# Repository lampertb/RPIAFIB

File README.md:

# RPIAFIB
AFIB Detection using Raspberry Pi Compute Module

This is a project created by Yifan Ge and Ben Lampert for the CS241 Embedded Workshop class(http://web.stanford.edu/class/cs241/). The intention is to create an open source AFIB detection wearable which can be used to diagnose patients with the condition.

Please reference the instructable for more information on assembling the board.
http://www.instructables.com/id/rPI-Atrial-Fibrillation-Detection-Board/

To install run

sudo sh ./install.sh

Run software:
cd Software
sudo ./execute_afib_detect

Todo:
Software:
-Improve ECG Capture code
-Improve integration between the algorithm detection and sampling code
Hardware:
-Lipo charger circuit does not allow for the board to be powered while charging the LED, need to find a solution for this. Integrated charger?

USE AT YOUR OWN RISK: This project involves ECG measurements which can be dangerous if not done correctly. It is your responsibility to evaluate your own medical and physical condition, or that of your clients, and to independently determine whether to perform, use or adapt any of the information or content on this repository. By voluntarily undertaking the project displayed on this website, you assume the risk of any resulting injury.

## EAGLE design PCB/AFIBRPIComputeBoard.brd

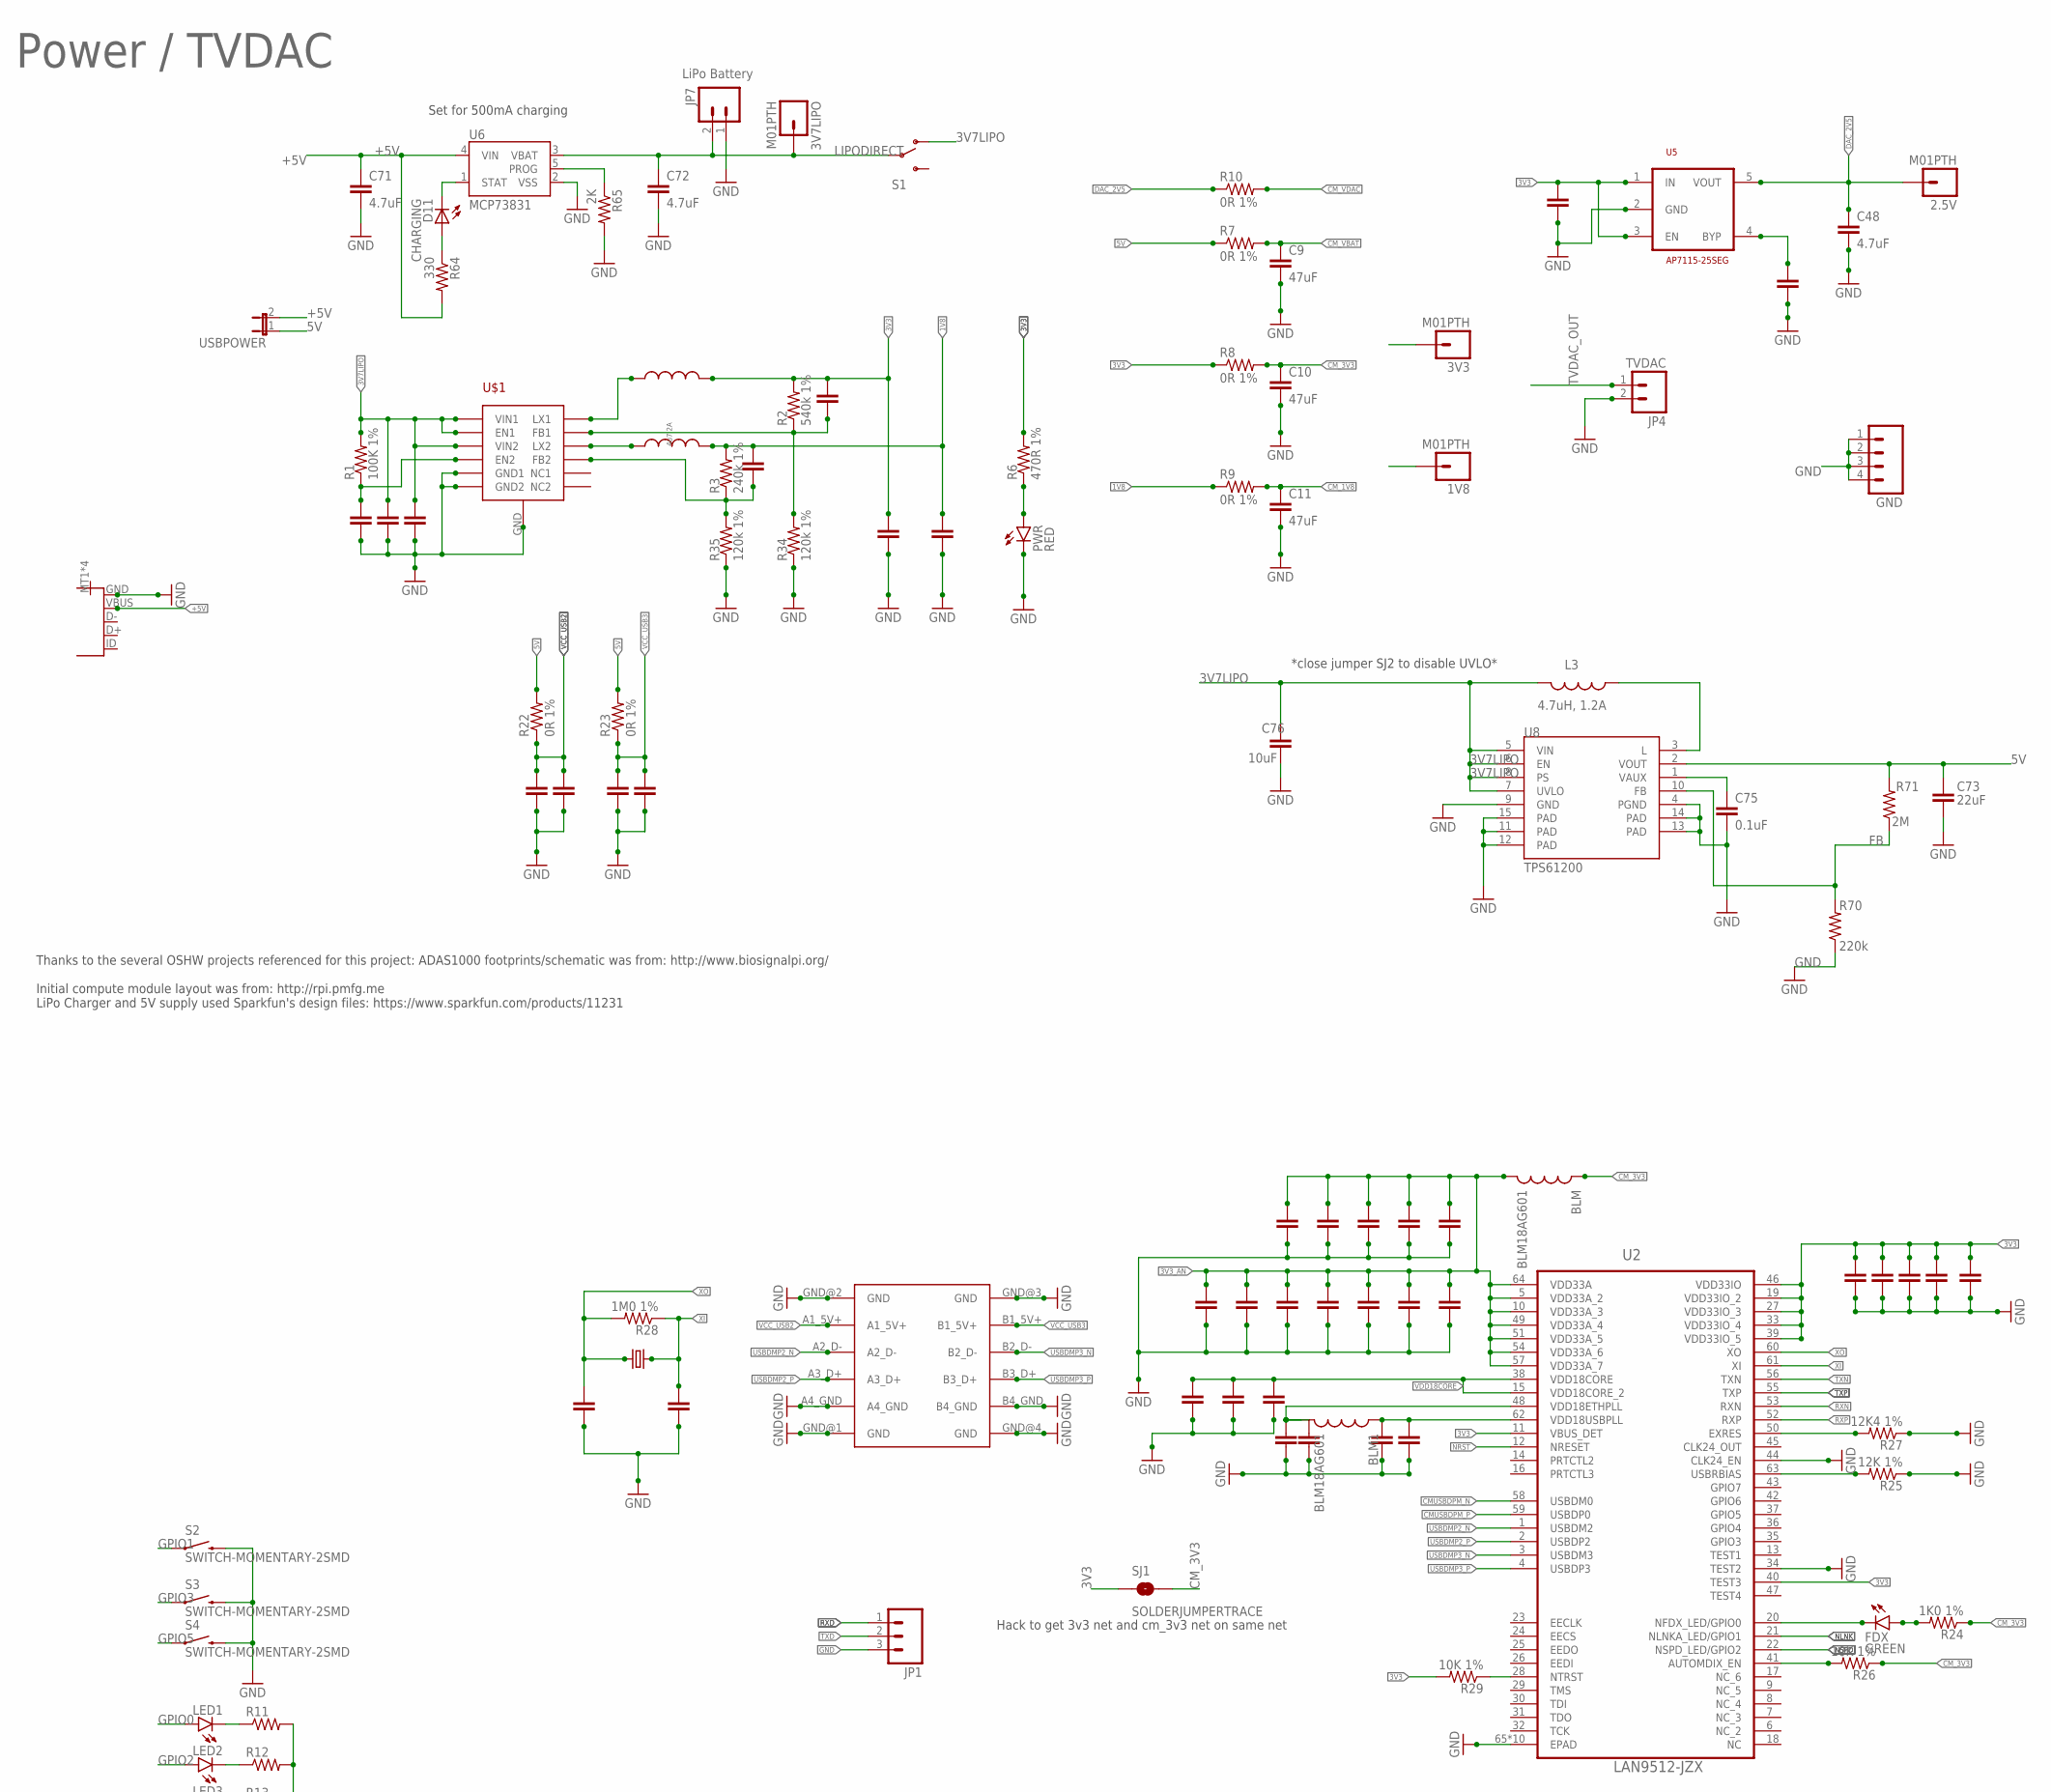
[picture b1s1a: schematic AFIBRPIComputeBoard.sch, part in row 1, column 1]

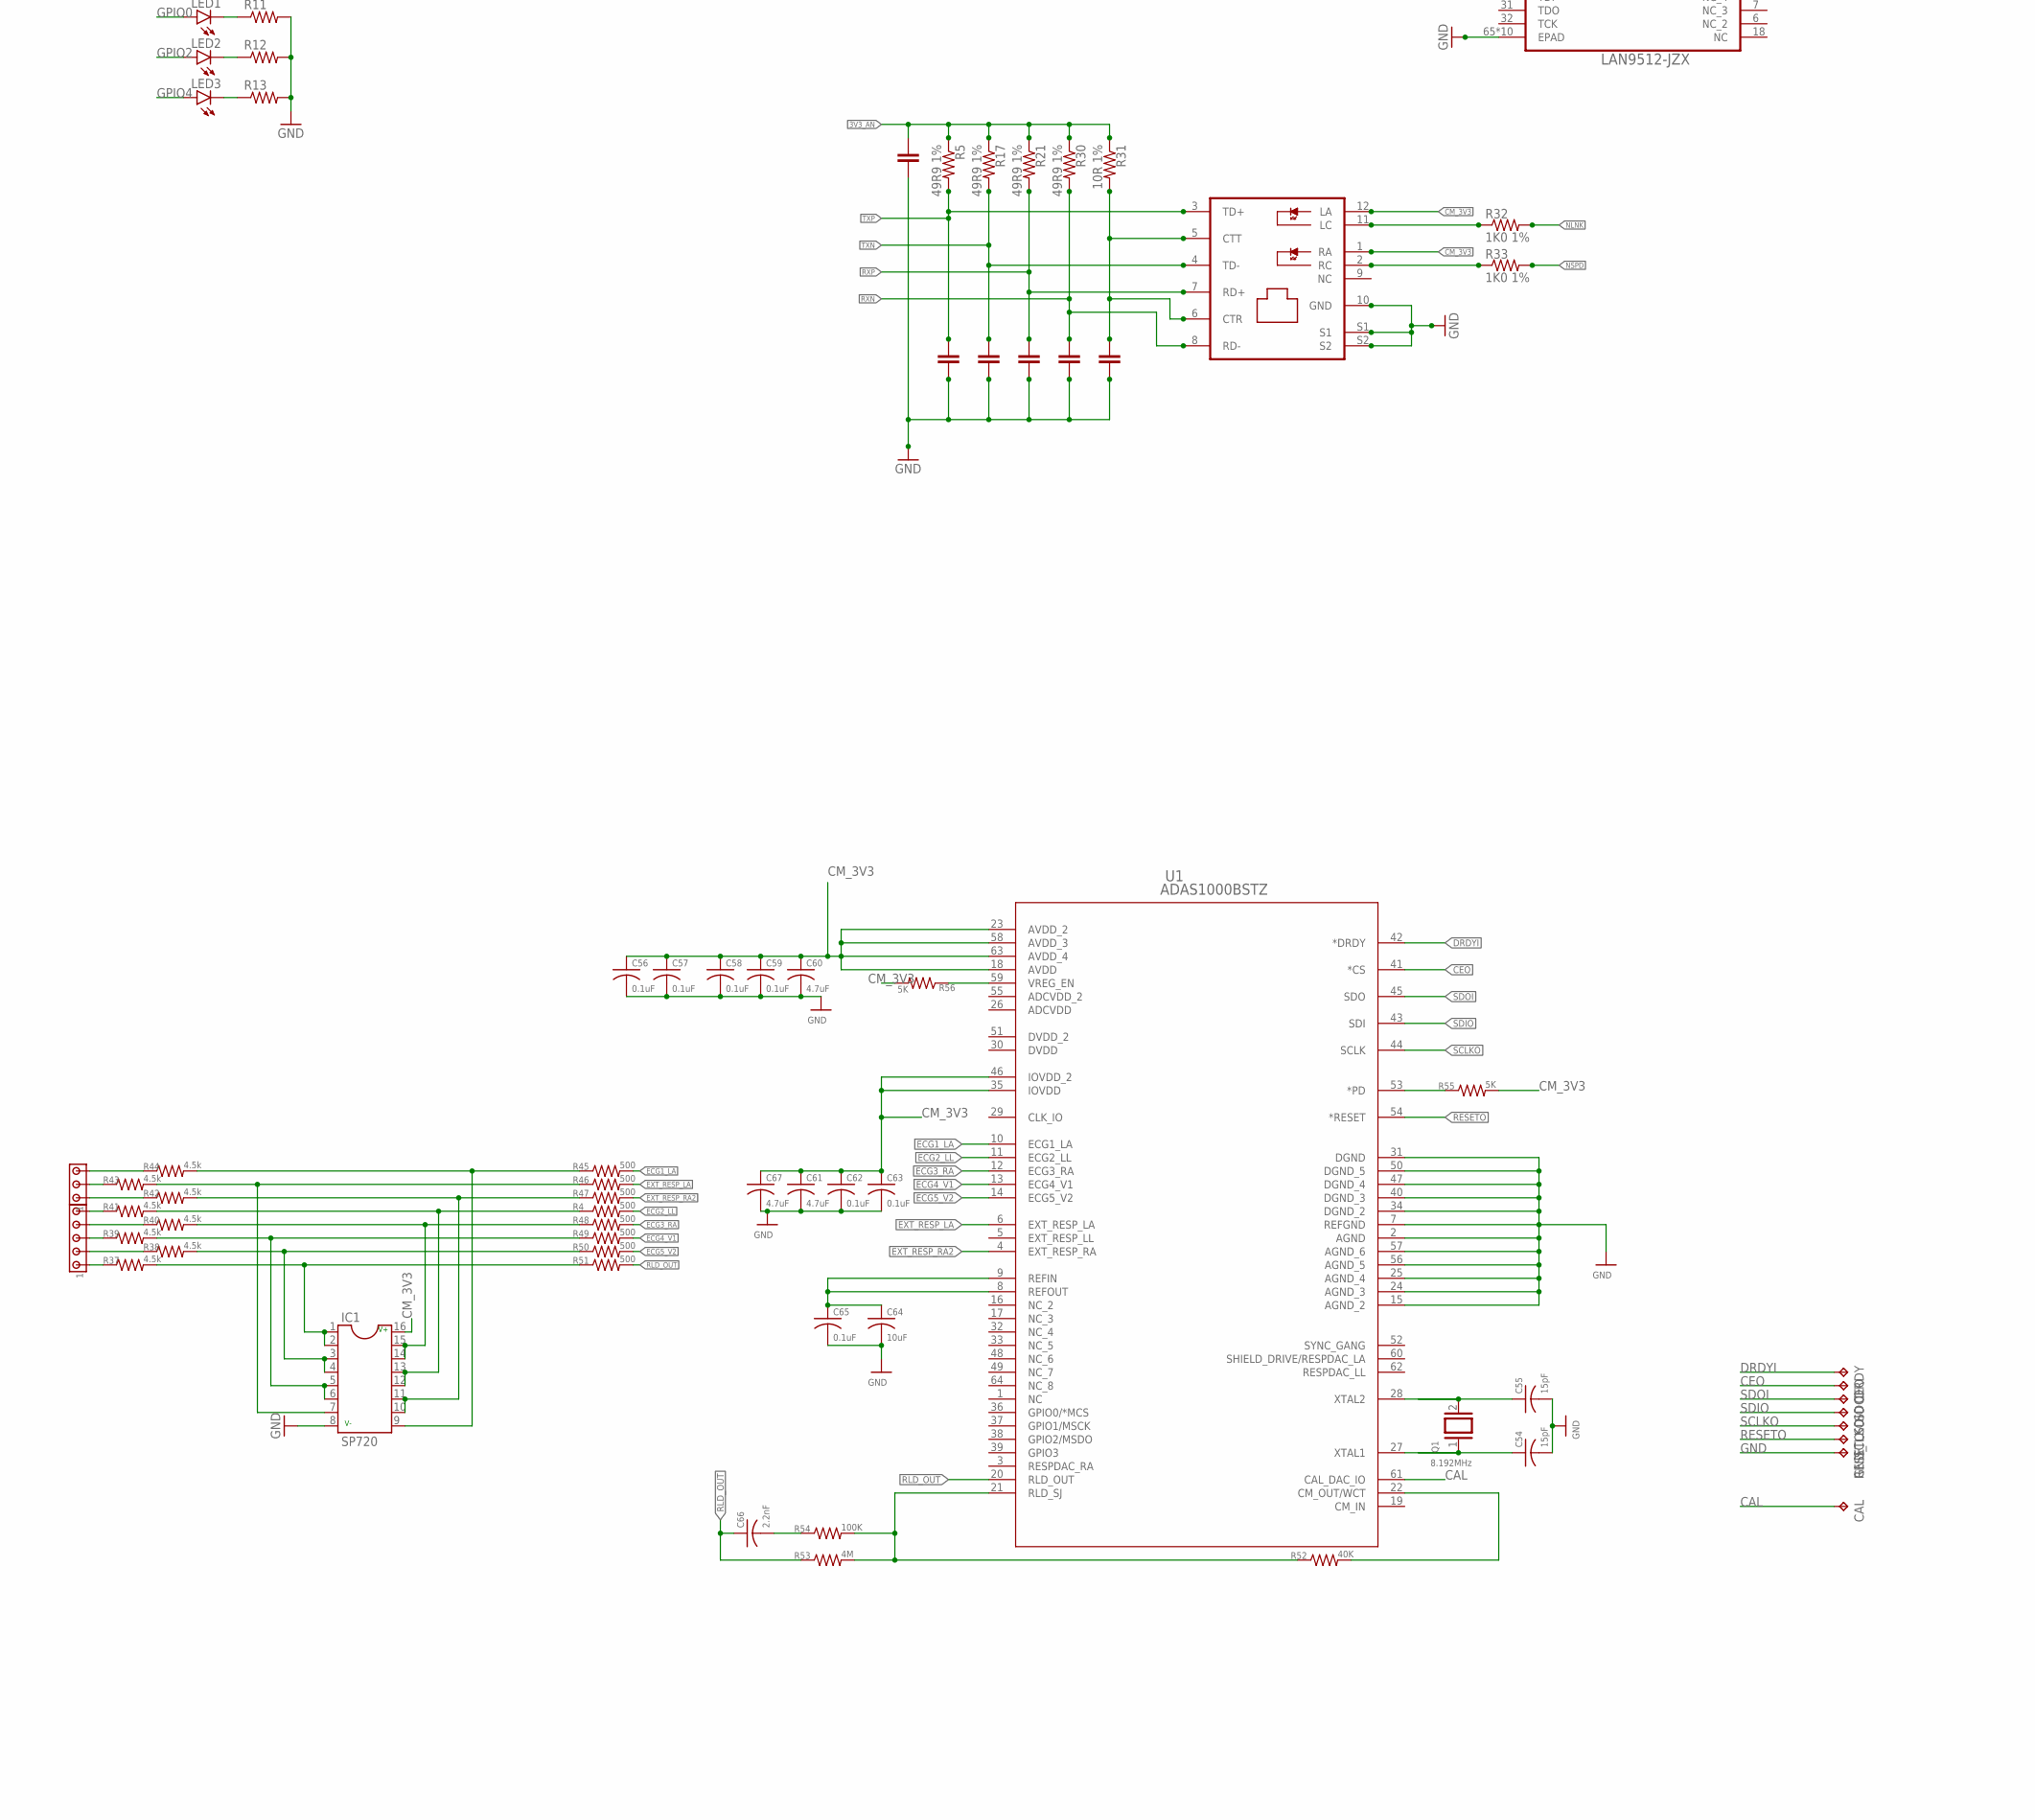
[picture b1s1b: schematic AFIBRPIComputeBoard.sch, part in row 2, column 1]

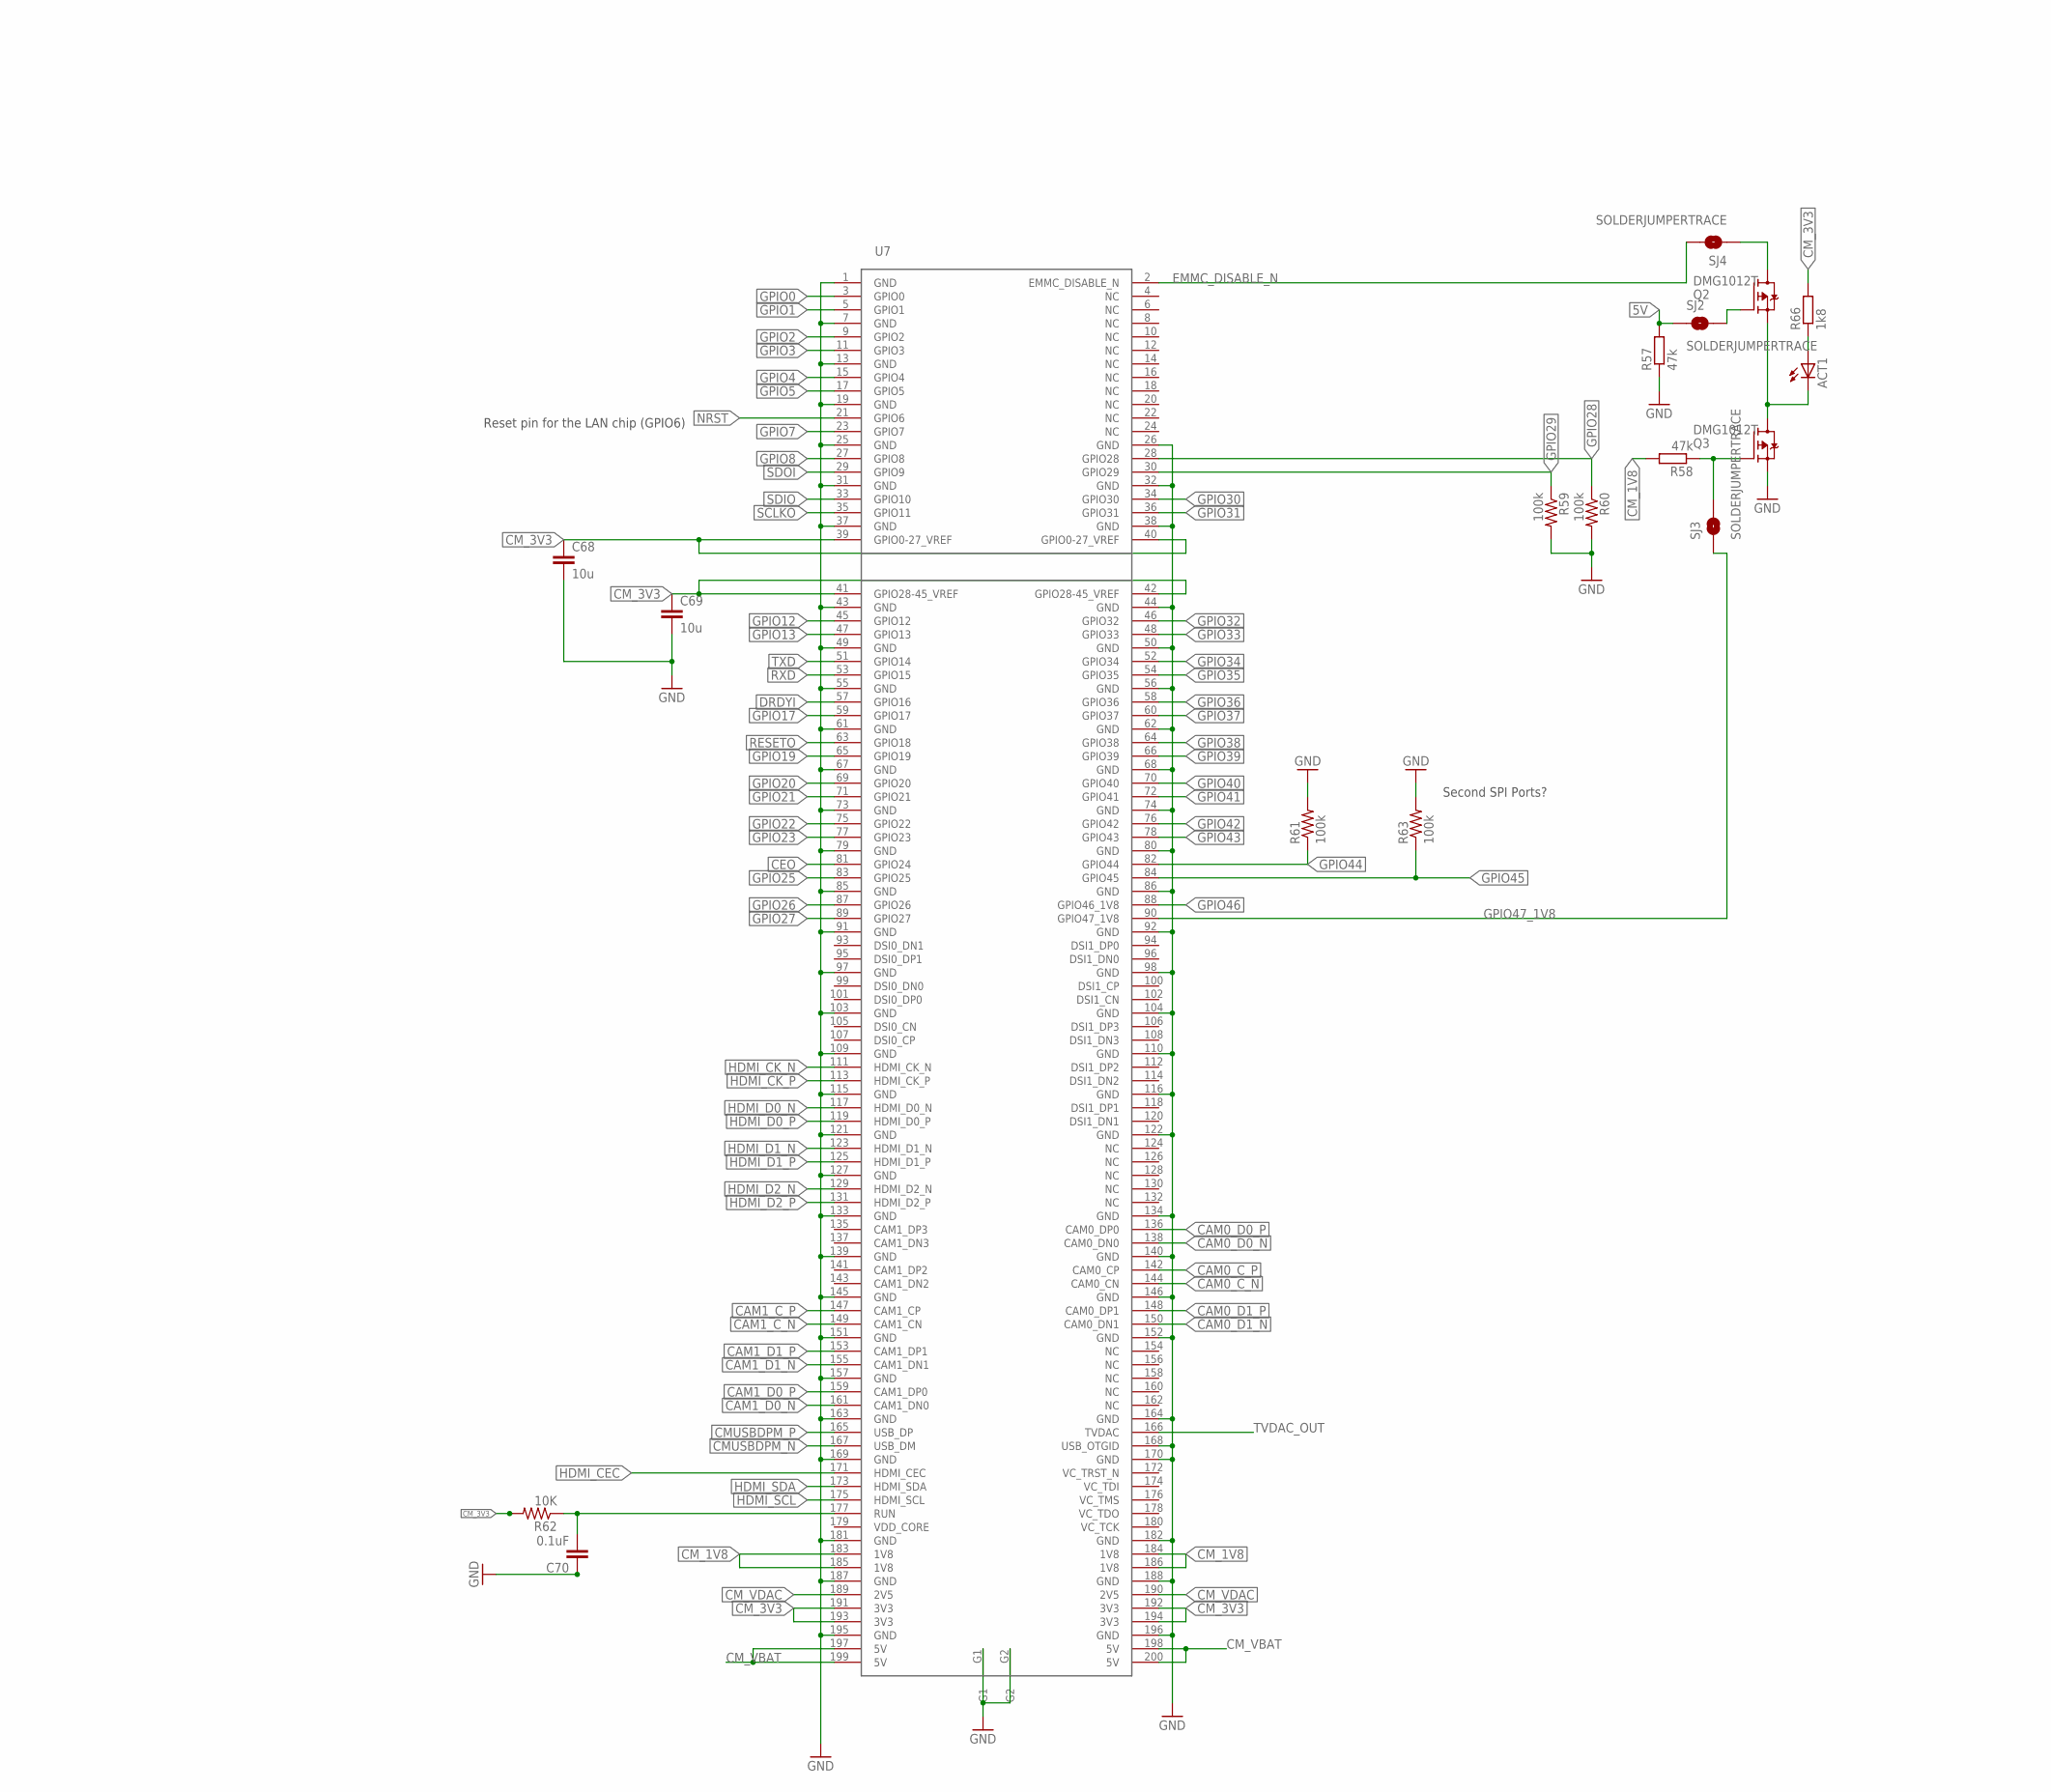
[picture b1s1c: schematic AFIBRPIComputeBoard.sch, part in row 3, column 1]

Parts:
1V8, 2.5V, 3V3, 3V7LIPO: M01PTH; 1X01
ACT1: LEDCHIP-LED0603; CHIP-LED0603
BLM, BLM1: BLM18AG601; 0603
C2, C17, C18, C19, C20, C22, C23, C24, C25, C26, C27, C28, C29, C30, C31, C32, C33, C34, C35, C39, C40, C41, C42, C46, C47: 100nF; 0402
C3, C4, C6, C8: 10uF; 0805
C5, C7, C16, C43: 15pf 50V 5%; 0402
C9, C10, C11: 47uF; 0603-CAP
C14, C15: 100uF 10v; 1206
C21, C36: 4u7; 0402
C37, C38: 12pf; 0402
C44: 47uf 10v; 0805
C45: 1uF; 0402
C48: 4.7uF; 0603-CAP
C49: 22nF; 0805
C50: 47uF 10V; 0805
C51, C52: 100pF; 0402
C54, C55: 15pF; C0805
C56, C57, C58, C59, C62, C63, C65: 0.1uF; C0805
C60, C61, C67: 4.7uF; C0805
C64: 10uF; C0805
C66: 2.2nF; C0805
C68, C69: 10u; 0603-CAP
C70, C75: 0.1uF; 0603-CAP
C71, C72: 4.7uF; 0402-CAP
C73: 22uF; 0603-CAP
C76: 10uF; 0603-CAP
CAL: TPPAD1-13; P1-13
CEO: TPPAD1-13; P1-13
D11: CHARGING; LED-0603
DRDY: TPPAD1-13; P1-13
FDX: GREEN; LED-0603
GND: M04PTH; 1X04
GND_: TPPAD1-13; P1-13
IC1: SP720; DIL16
J1: J3011; J30
J2: JUMPERS; 10X03MTA
J3: JUMPERS; 10X05MTA
JP1: M03PTH; 1X03
JP3: USB-IDMICRO; USB-MICRO
JP4: TVDAC; 1X02
JP7: LiPo Battery; JST-2-SMD
L1, L2: 4.7u 2A; SRN4018
L3: 4.7uH, 1.2A; CDRH2D09
LED1, LED2, LED3: LED0603; LED-0603
PWR: RED; LED-0603
Q1: 8.192MHz; QS
Q2, Q3: DMG1012T; SC75_INFINEON
R1: 100K 1%; 0402-RES
R2: 540k 1%; 0402-RES
R3: 240k 1%; 0402-RES
R4, R45, R46, R47, R48, R49, R50, R51: 500; 0603-RES
R5, R17, R21, R30: 49R9 1%; 0402-RES
R6: 470R 1%; 0402-RES
R7, R8, R9, R10, R22, R23: 0R 1%; 0603-RES
R11, R12, R13: RESISTOR0603; 0603-RES
R24, R32, R33: 1K0 1%; 0402-RES
R25: 12K 1%; 0402-RES
R26, R29: 10K 1%; 0402-RES
R27: 12K4 1%; 0402-RES
R28: 1M0 1%; 0402-RES
R31: 10R 1%; 0402-RES
R34, R35: 120k 1%; 0402-RES
R37, R38, R39, R40, R41, R42, R43, R44: 4.5k; 0603-RES
R52: 40K; 0603-RES
R53: 4M; 0603-RES
R54: 100K; 0603-RES
R55, R56: 5K; 0603-RES
R57, R58: 47k; R0603
R59, R60, R61, R63: 100k; 0603-RES
R62: 10K; 0603-RES
R64: 330; 0402-RES
R65: 2K; 0402-RES
R66: 1k8; R0603
R70: 220k; 0402-RES
R71: 2M; 0402-RES
RESETO: TPPAD1-13; P1-13
S1: SWITCH-SPDT-SMD-A; SWITCH-SPST-SMD-A
S2, S3, S4: SWITCH-MOMENTARY-2SMD; TACTILE-SWITCH-SMD
SCLKO: TPPAD1-13; P1-13
SDIO: TPPAD1-13; P1-13
SDOI: TPPAD1-13; P1-13
SJ1, SJ2, SJ3, SJ4: SOLDERJUMPERTRACE; SJ_2S-TRACE
U1: ADAS1000BSTZ; ST_64_2
U2: LAN9512-JZX; QFN50P900X900X100-65N
U5: AP7115-25SEG; SOT353
U6: MCP73831; SOT23-5
U7: RASPI; SO-DIMM
U8: TPS61200; QFN-10_PAD
U$1: WDFN-12L
USB1: 72309USB-TYPE-A; 72309
USBPOWER: JUMPER-2PTH; 1X02
Y1: CRYSTAL5X3; CRYSTAL-SMD-5X3

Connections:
1V8: C8.1, C52.1, L2.P$2 (2), R3.2, R9.1
3V3: C6.1, C21.1, C32.1, C33.1, C34.1, C35.1, C45.1, C51.1, L1.P$2 (2), R2.2, R6.2, R8.1, R29.2, SJ1.1, U2.11 (VBUS_DET), U2.19 (VDD33IO_2), U2.27 (VDD33IO_3), U2.33 (VDD33IO_4), U2.39 (VDD33IO_5), U2.40 (TEST3), U2.46 (VDD33IO), U5.1 (IN), U5.3 (EN)
3V3_AN: BLM.2, C17.1, C18.1, C19.1, C20.1, C22.1, C23.1, C24.1, C25.1, C26.1, C27.1, C28.1, C29.1, C46.1, R5.1, R17.1, R21.1, R30.1, R31.1, U2.5 (VDD33A_2), U2.10 (VDD33A_3), U2.49 (VDD33A_4), U2.51 (VDD33A_5), U2.54 (VDD33A_6), U2.57 (VDD33A_7), U2.64 (VDD33A)
3V7LIPO: C3.1, C4.1, C76.1, L3.P$2 (2), R1.2, S1.1 (O), U8.5 (VIN), U8.6 (EN), U8.7 (UVLO), U8.8 (PS), U$1.1 (VIN2), U$1.6 (EN1), U$1.7 (VIN1)
5V: C73.1, R7.1, R22.2, R23.2, R57.2, R71.2, SJ2.1, U8.2 (VOUT), USBPOWER.1
+5V: C71.1, JP3.VBUS, R64.2, U6.4 (VIN), USBPOWER.2
CAL: CAL.TP, U1.61 (CAL_DAC_IO)
CAM0_C_N: U7.144 (CAM0_CN)
CAM0_C_P: U7.142 (CAM0_CP)
CAM0_D0_N: U7.138 (CAM0_DN0)
CAM0_D0_P: U7.136 (CAM0_DP0)
CAM0_D1_N: U7.150 (CAM0_DN1)
CAM0_D1_P: U7.148 (CAM0_DP1)
CAM1_C_N: U7.149 (CAM1_CN)
CAM1_C_P: U7.147 (CAM1_CP)
CAM1_D0_N: U7.161 (CAM1_DN0)
CAM1_D0_P: U7.159 (CAM1_DP0)
CAM1_D1_N: U7.155 (CAM1_DN1)
CAM1_D1_P: U7.153 (CAM1_DP1)
CEO: CEO.TP, U1.41 (*CS), U7.81 (GPIO24)
CMUSBDPM_N: U2.58 (USBDM0), U7.167 (USB_DM)
CMUSBDPM_P: U2.59 (USBDP0), U7.165 (USB_DP)
CM_1V8: 1V8.1, C11.1, R9.2, R58.2, U7.183 (1V8), U7.184 (1V8), U7.185 (1V8), U7.186 (1V8)
CM_3V3: 3V3.1, BLM.1, C10.1, C56.1, C57.1, C58.1, C59.1, C60.1, C61.1, C62.1, C63.1, C67.1, C68.1, C69.1, IC1.16, J1.1 (RA), J1.12 (LA), R8.2, R24.1, R26.1, R55.2, R56.2, R62.2, R66.2, SJ1.2, U1.18 (AVDD), U1.23 (AVDD_2), U1.35 (IOVDD), U1.46 (IOVDD_2), U1.58 (AVDD_3), U1.63 (AVDD_4), U7.39 (GPIO0-27_VREF), U7.40 (GPIO0-27_VREF), U7.41 (GPIO28-45_VREF), U7.42 (GPIO28-45_VREF), U7.191 (3V3), U7.192 (3V3), U7.193 (3V3), U7.194 (3V3)
CM_VBAT: C9.1, R7.2, U7.197 (5V), U7.198 (5V), U7.199 (5V), U7.200 (5V)
CM_VDAC: R10.2, U7.189 (2V5), U7.190 (2V5)
DAC_2V5: 2.5V.1, C48.1, R10.1, U5.5 (VOUT)
DRDYI: DRDY.TP, U1.42 (*DRDY), U7.57 (GPIO16)
ECG1_LA: R45.2, U1.10 (ECG1_LA)
ECG2_LL: R4.2, U1.11 (ECG2_LL)
ECG3_RA: R48.2, U1.12 (ECG3_RA)
ECG4_V1: R49.2, U1.13 (ECG4_V1)
ECG5_V2: R50.2, U1.14 (ECG5_V2)
EMMC_DISABLE_N: SJ4.2, U7.2 (EMMC_DISABLE_N)
EXT_RESP_LA: R46.2, U1.6 (EXT_RESP_LA)
EXT_RESP_RA2: R47.2, U1.4 (EXT_RESP_RA)
FB: R70.2, R71.1, U8.10 (FB)
GND: C2.2, C3.2, C4.2, C5.2, C6.2, C7.2, C8.2, C9.2, C10.2, C11.2, C14.2, C15.2, C16.2, C17.2, C18.2, C19.2, C20.2, C21.2, C22.2, C23.2, C24.2, C25.2, C26.2, C27.2, C28.2, C29.2, C30.2, C31.2, C32.2, C33.2, C34.2, C35.2, C36.2, C37.2, C38.2, C39.2, C40.2, C41.2, C42.2, C43.2, C44.2, C45.2, C46.2, C47.2, C48.2, C49.2, C50.2, C54.2, C55.2, C56.2, C57.2, C58.2, C59.2, C60.2, C61.2, C62.2, C63.2, C64.2, C65.2, C67.2, C68.2, C69.2, C70.1, C71.2, C72.2, C73.2, C75.2, C76.2, GND.1, GND.2, GND.3, GND.4, GND_.TP, IC1.8, J1.10 (GND), J1.S1, J1.S2, JP1.3, JP3.GND, JP4.2, JP7.1, Q3.3 (S), R11.2, R12.2, R13.2, R25.1, R27.1, R34.1, R35.1, R57.1, R59.2, R60.2, R61.2, R63.2, R65.2, R70.1, S2.3 (2), S3.3 (2), S4.3 (2), U1.2 (AGND), U1.7 (REFGND), U1.15 (AGND_2), U1.24 (AGND_3), U1.25 (AGND_4), U1.31 (DGND), U1.34 (DGND_2), U1.40 (DGND_3), U1.47 (DGND_4), U1.50 (DGND_5), U1.56 (AGND_5), U1.57 (AGND_6), U2.34 (TEST2), U2.44 (CLK24_EN), U2.65 (EPAD), U2.GND@1 (EPAD), U2.GND@2 (EPAD), U2.GND@3 (EPAD), U2.GND@4 (EPAD), U2.GND@5 (EPAD), U2.GND@6 (EPAD), U2.GND@7 (EPAD), U2.GND@8 (EPAD), U2.GND@9 (EPAD), U5.2 (GND), U6.2 (VSS), U7.1 (GND), U7.7 (GND), U7.13 (GND), U7.19 (GND), U7.25 (GND), U7.26 (GND), U7.31 (GND), U7.32 (GND), U7.37 (GND), U7.38 (GND), U7.43 (GND), U7.44 (GND), U7.49 (GND), U7.50 (GND), U7.55 (GND), U7.56 (GND), U7.61 (GND), U7.62 (GND), U7.67 (GND), U7.68 (GND), U7.73 (GND), U7.74 (GND), U7.79 (GND), U7.80 (GND), U7.85 (GND), U7.86 (GND), U7.91 (GND), U7.92 (GND), U7.97 (GND), U7.98 (GND), U7.103 (GND), U7.104 (GND), U7.109 (GND), U7.110 (GND), U7.115 (GND), U7.116 (GND), U7.121 (GND), U7.122 (GND), U7.127 (GND), U7.133 (GND), U7.134 (GND), U7.139 (GND), U7.140 (GND), U7.145 (GND), U7.146 (GND), U7.151 (GND), U7.152 (GND), U7.157 (GND), U7.163 (GND), U7.164 (GND), U7.168 (USB_OTGID), U7.169 (GND), U7.170 (GND), U7.181 (GND), U7.182 (GND), U7.187 (GND), U7.188 (GND), U7.195 (GND), U7.196 (GND), U7.G1, U7.G2, U8.4 (PGND), U8.9 (GND), U8.11 (PAD), U8.12 (PAD), U8.13 (PAD), U8.14 (PAD), U8.15 (PAD), U$1.3 (GND1), U$1.9 (GND2), U$1.GND, USB1.A4_GND, USB1.B4_GND, USB1.GND@1 (GND), USB1.GND@2 (GND), USB1.GND@3 (GND), USB1.GND@4 (GND)
GPIO0: LED1.A, U7.3 (GPIO0)
GPIO1: S2.1, U7.5 (GPIO1)
GPIO2: LED2.A, U7.9 (GPIO2)
GPIO3: S3.1, U7.11 (GPIO3)
GPIO4: LED3.A, U7.15 (GPIO4)
GPIO5: S4.1, U7.17 (GPIO5)
GPIO7: U7.23 (GPIO7)
GPIO8: U7.27 (GPIO8)
GPIO12: U7.45 (GPIO12)
GPIO13: U7.47 (GPIO13)
GPIO17: U7.59 (GPIO17)
GPIO19: U7.65 (GPIO19)
GPIO20: U7.69 (GPIO20)
GPIO21: U7.71 (GPIO21)
GPIO22: U7.75 (GPIO22)
GPIO23: U7.77 (GPIO23)
GPIO25: U7.83 (GPIO25)
GPIO26: U7.87 (GPIO26)
GPIO27: U7.89 (GPIO27)
GPIO28: R60.1, U7.28 (GPIO28)
GPIO29: R59.1, U7.30 (GPIO29)
GPIO30: U7.34 (GPIO30)
GPIO31: U7.36 (GPIO31)
GPIO32: U7.46 (GPIO32)
GPIO33: U7.48 (GPIO33)
GPIO34: U7.52 (GPIO34)
GPIO35: U7.54 (GPIO35)
GPIO36: U7.58 (GPIO36)
GPIO37: U7.60 (GPIO37)
GPIO38: U7.64 (GPIO38)
GPIO39: U7.66 (GPIO39)
GPIO40: U7.70 (GPIO40)
GPIO41: U7.72 (GPIO41)
GPIO42: U7.76 (GPIO42)
GPIO43: U7.78 (GPIO43)
GPIO44: R61.1, U7.82 (GPIO44)
GPIO45: R63.1, U7.84 (GPIO45)
GPIO46: U7.88 (GPIO46_1V8)
GPIO47_1V8: SJ3.1, U7.90 (GPIO47_1V8)
HDMI_CEC: U7.171 (HDMI_CEC)
HDMI_CK_N: U7.111 (HDMI_CK_N)
HDMI_CK_P: U7.113 (HDMI_CK_P)
HDMI_D0_N: U7.117 (HDMI_D0_N)
HDMI_D0_P: U7.119 (HDMI_D0_P)
HDMI_D1_N: U7.123 (HDMI_D1_N)
HDMI_D1_P: U7.125 (HDMI_D1_P)
HDMI_D2_N: U7.129 (HDMI_D2_N)
HDMI_D2_P: U7.131 (HDMI_D2_P)
HDMI_SCL: U7.175 (HDMI_SCL)
HDMI_SDA: U7.173 (HDMI_SDA)
JUMPERS: J2.1, R42.1
LIPODIRECT: 3V7LIPO.1, C72.1, JP7.2, S1.2, U6.3 (VBAT)
unnamed: L1.P$1 (1), U$1.8 (LX1)
unnamed: C51.2, R2.1, R34.2, U$1.4 (FB1)
unnamed: C2.1, R1.1, U$1.12 (EN2)
unnamed: L2.P$1 (1), U$1.2 (LX2)
unnamed: C52.2, R3.1, R35.2, U$1.10 (FB2)
unnamed: PWR.A, R6.1
unnamed: Q2.2 (D), SJ4.1
unnamed: Q3.1 (G), R58.1, SJ3.2
unnamed: LED3.C, R13.1
unnamed: LED2.C, R12.1
unnamed: FDX.A, R24.2
unnamed: LED1.C, R11.1
unnamed: Q2.1 (G), SJ2.2
unnamed: R25.2, U2.63 (USBRBIAS)
unnamed: J3.1, R37.1
unnamed: C47.1, U5.4 (BYP)
unnamed: BLM1.1, C41.1, C42.1, U2.62 (VDD18USBPLL)
unnamed: BLM1.2, C39.1, C40.1, U2.48 (VDD18ETHPLL)
unnamed: R26.2, U2.41 (AUTOMDIX_EN)
unnamed: R27.2, U2.50 (EXRES)
unnamed: R29.1, U2.28 (NTRST)
unnamed: J1.11 (LC), R32.1
unnamed: J1.2 (RC), R33.1
unnamed: C49.1, J1.5 (CTT), J1.6 (CTR), R31.2
unnamed: FDX.C, U2.20 (NFDX_LED/GPIO0)
unnamed: J3.2, R38.1
unnamed: J3.3, R39.1
unnamed: J3.4, R40.1
unnamed: J3.5, R41.1
unnamed: J2.2, R43.1
unnamed: J2.3, R44.1
unnamed: IC1.9, R44.2, R45.1
unnamed: IC1.7, R43.2, R46.1
unnamed: IC1.3, IC1.4, R38.2, R50.1
unnamed: IC1.5, IC1.6, R39.2, R49.1
unnamed: IC1.1, IC1.2, R37.2, R51.1
unnamed: IC1.14, IC1.15, R40.2, R48.1
unnamed: IC1.12, IC1.13, R4.1, R41.2
unnamed: IC1.10, IC1.11, R42.2, R47.1
unnamed: C55.1, Q1.2, U1.28 (XTAL2)
unnamed: C54.1, Q1.1, U1.27 (XTAL1)
unnamed: C66.2, R54.1
unnamed: R55.1, U1.53 (*PD)
unnamed: R56.1, U1.59 (VREG_EN)
unnamed: R52.2, U1.22 (CM_OUT/WCT)
unnamed: C64.1, C65.1, U1.8 (REFOUT), U1.9 (REFIN)
unnamed: R52.1, R53.2, R54.2, U1.21 (RLD_SJ)
unnamed: ACT1.C, Q2.3 (S), Q3.2 (D)
unnamed: D11.A, R64.1
unnamed: L3.P$1 (1), U8.3 (L)
unnamed: C75.1, U8.1 (VAUX)
unnamed: ACT1.A, R66.1
NLNK: R32.2, U2.21 (NLNKA_LED/GPIO1)
NRST: U2.12 (NRESET), U7.21 (GPIO6)
NSPD: R33.2, U2.22 (NSPD_LED/GPIO2)
PROG: R65.1, U6.5 (PROG)
RESETO: RESETO.TP, U1.54 (*RESET), U7.63 (GPIO18)
RLD_OUT: C66.1, R51.2, R53.1, U1.20 (RLD_OUT)
RUNPIN: C70.2, R62.1, U7.177 (RUN)
RXD: JP1.1, U7.53 (GPIO15)
RXN: C43.1, J1.8 (RD-), R30.2, U2.53 (RXN)
RXP: C16.1, J1.7 (RD+), R21.2, U2.52 (RXP)
SCLKO: SCLKO.TP, U1.44 (SCLK), U7.35 (GPIO11)
SDIO: SDIO.TP, U1.43 (SDI), U7.33 (GPIO10)
SDOI: SDOI.TP, U1.45 (SDO), U7.29 (GPIO9)
STAT: D11.C, U6.1 (STAT)
TVDAC_OUT: JP4.1, U7.166 (TVDAC)
TXD: JP1.2, U7.51 (GPIO14)
TXN: C7.1, J1.4 (TD-), R17.2, U2.56 (TXN)
TXP: C5.1, J1.3 (TD+), R5.2, U2.55 (TXP)
USBDMP2_N: U2.1 (USBDM2), USB1.A2_D-
USBDMP2_P: U2.2 (USBDP2), USB1.A3_D+
USBDMP3_N: U2.3 (USBDM3), USB1.B2_D-
USBDMP3_P: U2.4 (USBDP3), USB1.B3_D+
VCC_USB2: C14.1, C44.1, R22.1, USB1.A1_5V+
VCC_USB3: C15.1, C50.1, R23.1, USB1.B1_5V+
VDD18CORE: C30.1, C31.1, C36.1, U2.15 (VDD18CORE_2), U2.38 (VDD18CORE)
XI: C37.1, R28.1, U2.61 (XI), Y1.3 (2)
XO: C38.1, R28.2, U2.60 (XO), Y1.1

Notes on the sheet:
Power / TVDAC
Second SPI Ports?
Reset pin for the LAN chip (GPIO6)
Set for 500mA charging
*close jumper SJ2 to disable UVLO*
Hack to get 3v3 net and cm_3v3 net on same net
Thanks to the several OSHW projects referenced for this project: ADAS1000 footprints/schematic was from: http://www.biosignalpi.org/ Initial compute module layout was from: http://rpi.pmfg.me LiPo Charger and 5V supply used Sparkfun's design files: https://www.sparkfun.com/products/11231

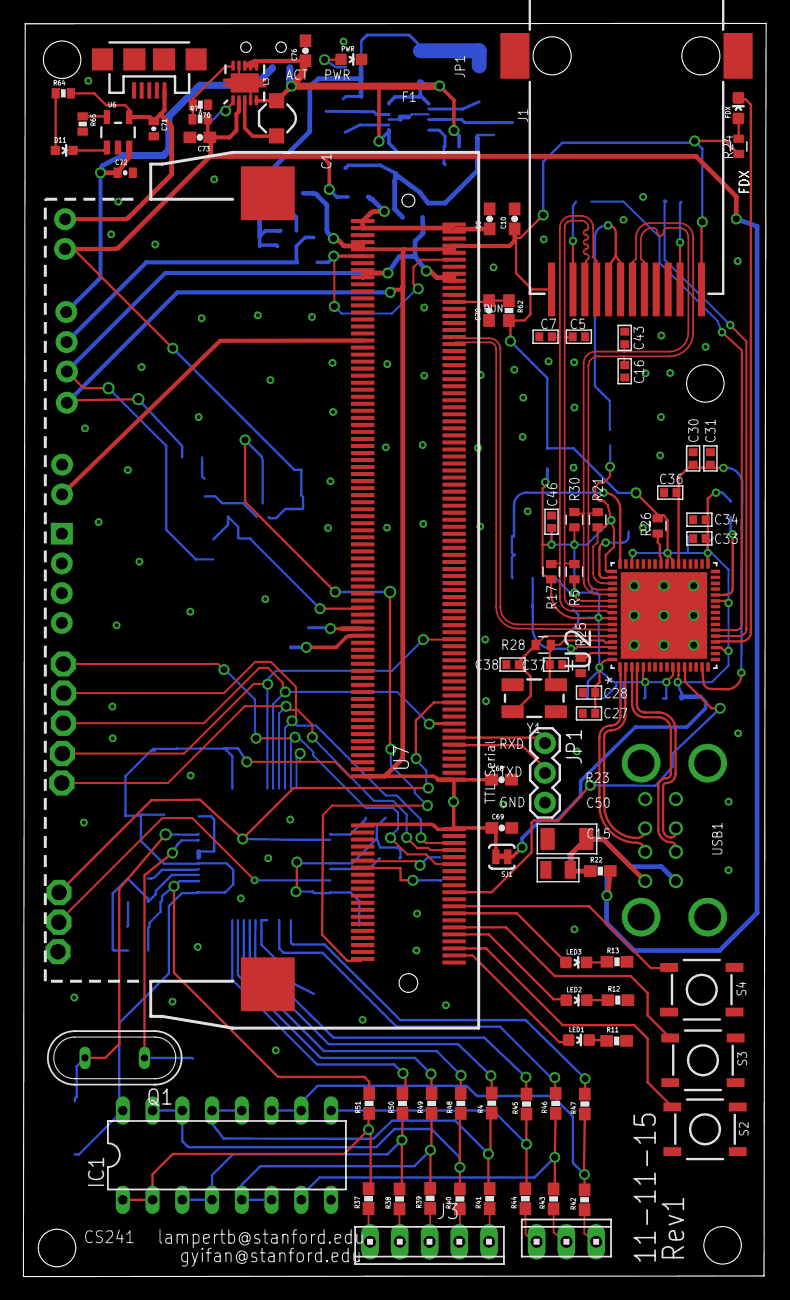
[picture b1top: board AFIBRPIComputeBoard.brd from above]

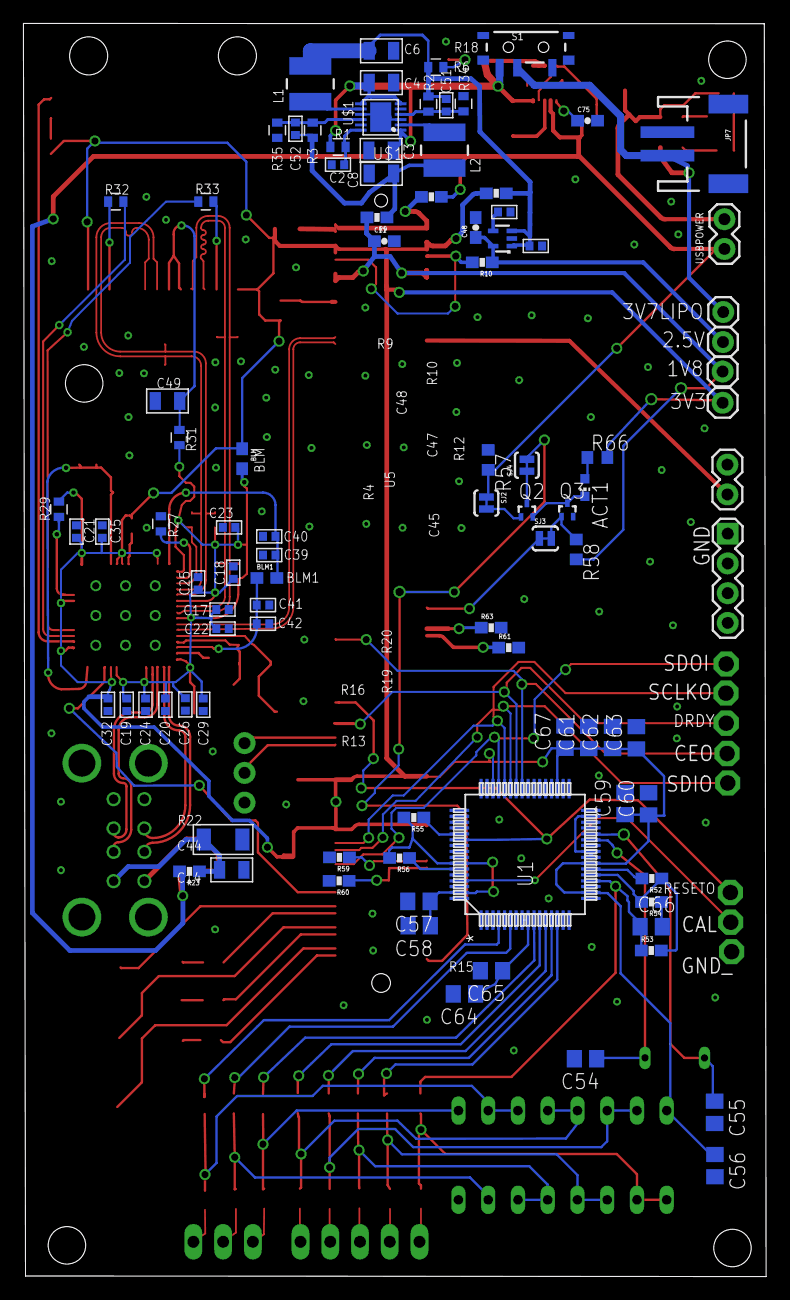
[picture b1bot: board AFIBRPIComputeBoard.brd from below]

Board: 2 copper layers, 63.4 x 107.0 mm, 186 parts (103 on the bottom side), 118 nets.

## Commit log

2015-12-06 Added PCB layout
2015-12-06 Added images of board and updated the readme
2015-12-06 Fixed link on README
2015-12-06 Added first pass at boot script
2015-12-06 Added run.sh and fixed boot options
2015-12-06 Updated install.sh to add python-dev
2015-12-06 Added Software package
2015-12-06 Fixed run.sh to include the afib_executable reference
2015-12-06 Added link for instructable
2015-12-07 Added disclaimer of liability
2015-12-07 Modified disclaimer

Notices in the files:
parts and their libraries:
SparkFun-LED: Licensing: Creative Commons ShareAlike 4.0 International - https://creativecommons.org/licenses/by-sa/4.0
